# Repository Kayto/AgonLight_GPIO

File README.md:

# AgonLight_GPIO

## Background
Agon Light is a compact low-cost board that is both a microcomputer and a BASIC-programmed microcontroller. It is intended to be easily hackable and allow interfacing with the outside world. It features 20x GPIO, plus SPI, I2C, UART for serial communication and allows a great opportunity for learning and experimentation.

## Introduction 

This repo is intended to provide some simple add on boards for gpio examples and experiments. Although I am of the 8 bit vintage, I consider myself a novice. I enjoy hardware making as a way to better understand the inner hardware workings and to ultimately improve my coding. All is a work in progress and is open to contributions and ideas, within the stated aims and limitations of this project.

## Aims
* Provide a range of simple IO hardware to aid coding in BBC BASIC.
* To be useful in gaining a general understanding of GPIO usage and real world interfacing.
* Stick to the general GPIOs only.
* Avoid cables and breadboards and try to fit a standardised form factor. In this case a plugable "faceplate" for the exiting gpio port. The board should avoid constraining any existing ports and access.
* Ideally, provide onboard visual feedback to aid learning.
* Avoid additional hardware processing on the add on board. Keeping access to the low level hardware prevents adding more complications when learning. I.e. GALs, additional controller ICs are to be avoided.

## The PCBs

KiCad, Schematics and Gerbers are provided. Renders of the boards are shown in the KiCad directory. Please review before making a commitment. No warranties or support are provided. As of this date PCBs are not yet tested but I will mark as such once done.

#### #1 - The Blinkenlight. - tested working

Every 8 bit computer needs blinky lights. Not only do they look like good, they are useful for debugging and understanding what is going on at a bit level.
The Blinkenlight PCB is pretty much the breadboard example from the official documentation but without the fiddly wires. It directly plugs into the GPIO header and provides an easily viewable "faceplate". This presents the form for future boards.

#### #2 - 7 segment display. - tested working

This is a single 7 segment display linked to the Port C GPIOs. Allows a simple message display with a delay. Ok its only single digits but something to build on.
A caution on this is that you need a 7 segment display to suit the pin out (they do vary). Review the schematics, Pin 3 and 8 are power.I have provided a solder jumper for setting of common anode and common cathode displays. Note that for common anode the coding assumes a LOW signal for on and HIGH for off.

#### #3 - Double Seven

**In progress.**

This is a **double** 7 segment display linked to the Port C GPIOs for data and 2No. Port D GPIOs to do the multiplexing.
To save space resistor networks are used instead of individual resistors.

#### #4 - Moody. - tested working

This is an RGB LED linked to the Port C GPIOs, 2No. push buttons are also provided. The two push buttons on PC_3 and PC_4 are to establish some input and mode switching capability. 

## The Code

I have created some code to introduce the boards. As said, coding is not my strength so excuse the code, in some cases its not a great example but enough to get things going and for a challenge to improve.
To view the code add the .BBC files to the SD card and load via BBC BASIC then type LIST.

| Board | Code | Description |
|:----------|:-------------|:-----|
|[#1_Blinkenlight](https://github.com/Kayto/AgonLight_GPIO/tree/main/KiCad/%231_Blinkenlight) | [PortC_blink.bbc](https://github.com/Kayto/AgonLight_GPIO/tree/main/Code) | select individual LEDs, set number of blinks and speed. |
|[#1_Blinkenlight](https://github.com/Kayto/AgonLight_GPIO/tree/main/KiCad/%231_Blinkenlight) | [gpioknight.bbc](https://github.com/Kayto/AgonLight_GPIO/tree/main/Code)| Some blinky patterns. Excuse the code, its a bad example with lots of inefficient duplication to get things done. The **challenge** is open to simplify this, perhaps a data array for the gpio commands and a single procedure for the delay?|
|[#1_Blinkenlight](https://github.com/Kayto/AgonLight_GPIO/tree/main/KiCad/%231_Blinkenlight) | [random8blink.bbc](https://github.com/Kayto/AgonLight_GPIO/tree/main/Code)| An easy change to PortC-Blink, uses the random function and fixed blink speed to just randomly blink the 8 LEDs!|
|[#2_seven_segment](https://github.com/Kayto/AgonLight_GPIO/tree/main/KiCad/%232_7Segment)|  [diceroll.bbc](https://github.com/Kayto/AgonLight_GPIO/tree/main/Code) | A random 1-6 generator for board games, handy. | 
|[#2_seven_segment](https://github.com/Kayto/AgonLight_GPIO/tree/main/KiCad/%232_7Segment)|  [counter.bbc](https://github.com/Kayto/AgonLight_GPIO/tree/main/Code) | A single digit counter, you're welcome. | 
|[#4_Moody](https://github.com/Kayto/AgonLight_GPIO/tree/main/KiCad/%234_Moody)|  [moodyfade.bbc](https://github.com/Kayto/AgonLight_GPIO/tree/main/Code) | An RGB fade using some crude PWM in BBC BASIC. | 
|[#4_Moody](https://github.com/Kayto/AgonLight_GPIO/tree/main/KiCad/%234_Moody)|  [moodybutton.bbc](https://github.com/Kayto/AgonLight_GPIO/tree/main/Code) | The RGB fade but now includes buttons. Button A for on and off. Button B to increase the fade speed.| 

## Disclaimer & Credits

Just a note that I am not in any way affiliated or linked with the Agon project.
I am just an aspiring maker, sharing hobbyist builds.
Thanks to the Agon project and supporters.

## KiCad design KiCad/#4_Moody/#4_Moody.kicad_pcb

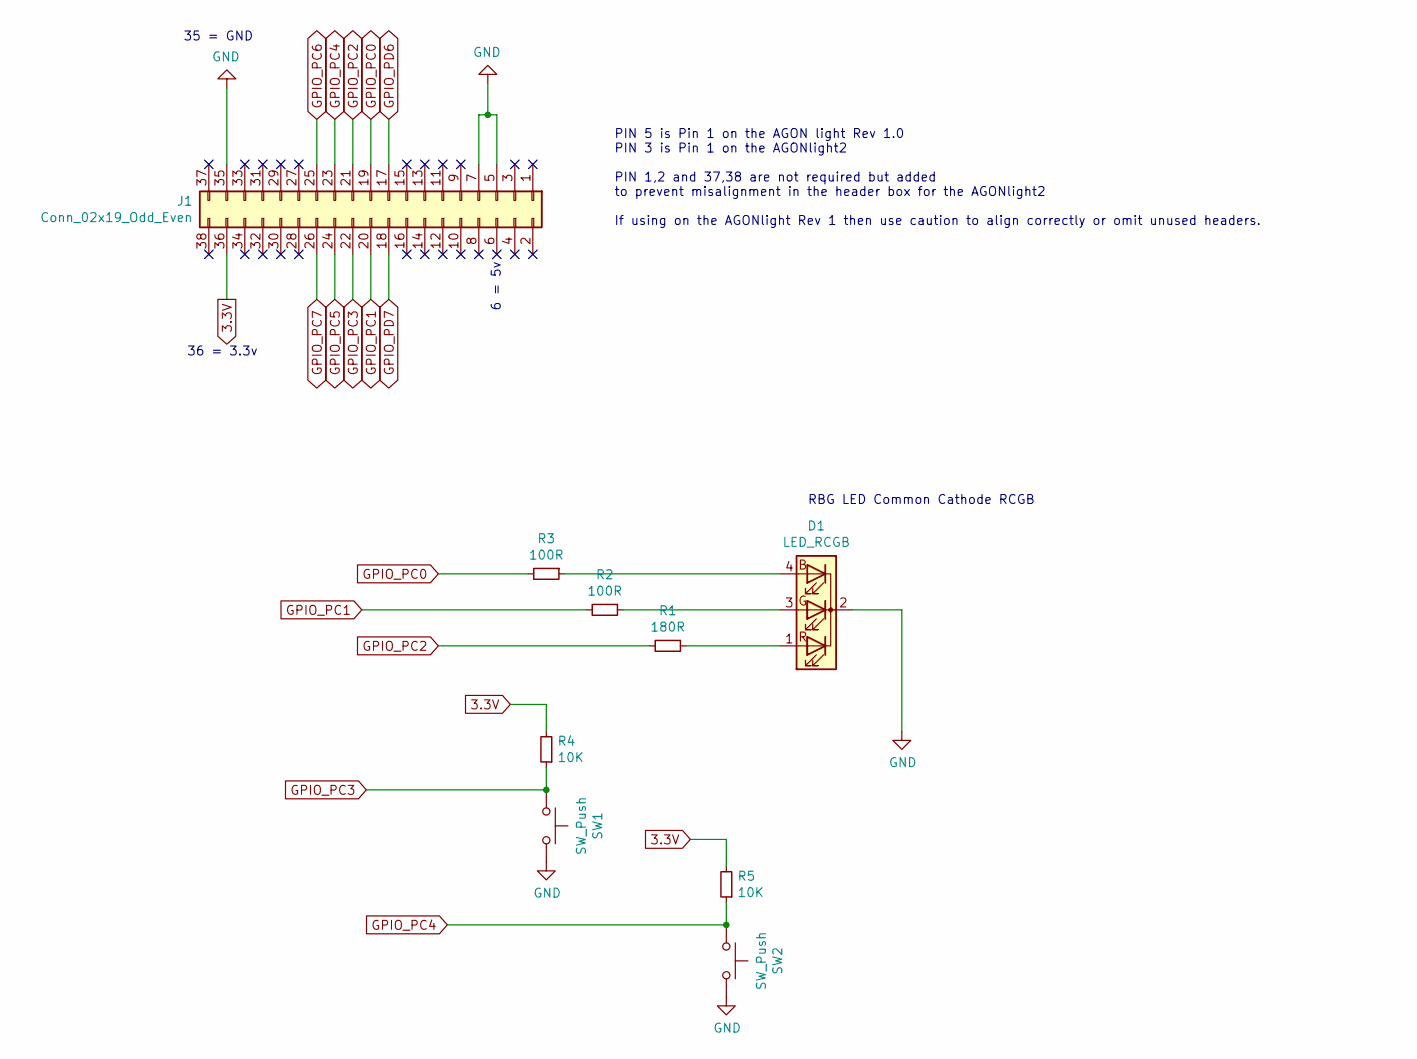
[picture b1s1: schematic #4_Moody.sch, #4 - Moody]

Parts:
D1: LED_RCGB; LED_D5.0mm-4_RGB
J1: Conn_02x19_Odd_Even; PinSocket_2x19_P2.54mm_Vertical
R1: 180R; R_Axial_DIN0207_L6.3mm_D2.5mm_P7.62mm_Horizontal
R2, R3: 100R; R_Axial_DIN0207_L6.3mm_D2.5mm_P7.62mm_Horizontal
R4, R5: 10K; R_Axial_DIN0207_L6.3mm_D2.5mm_P7.62mm_Horizontal
SW1, SW2: SW_Push; SW_PUSH_6mm_H4.3mm

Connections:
3.3V: J1.36, R4.2, R5.2
GND: D1.2 (K), J1.5, J1.7, J1.35, SW1.2, SW2.2
GPIO_PC0: J1.19, R3.2
GPIO_PC1: J1.20, R2.2
GPIO_PC2: J1.21, R1.2
GPIO_PC3: J1.22, R4.1, SW1.1
GPIO_PC4: J1.23, R5.1, SW2.1
GPIO_PC5: J1.24
GPIO_PC6: J1.25
GPIO_PC7: J1.26
GPIO_PD6: J1.17
GPIO_PD7: J1.18
unnamed: D1.1 (RA), R1.1
unnamed: D1.3 (GA), R2.1
unnamed: D1.4 (BA), R3.1

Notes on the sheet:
PIN 5 is Pin 1 on the AGON light Rev 1.0 PIN 3 is Pin 1 on the AGONlight2 PIN 1,2 and 37,38 are not required but added to prevent misalignment in the header box for the AGONlight2 If using on the AGONlight Rev 1 then use caution to align correctly or omit unused headers.
35 = GND
36 = 3.3v
6 = 5v
RBG LED Common Cathode RCGB

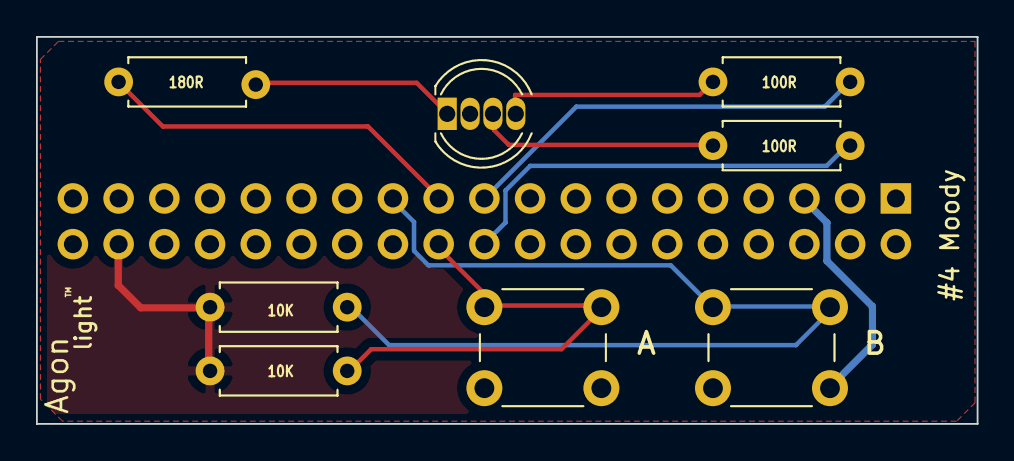
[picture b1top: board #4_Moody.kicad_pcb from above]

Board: 2 copper layers, 52.3 x 21.5 mm, 9 parts (1 on the bottom side), 10 nets.

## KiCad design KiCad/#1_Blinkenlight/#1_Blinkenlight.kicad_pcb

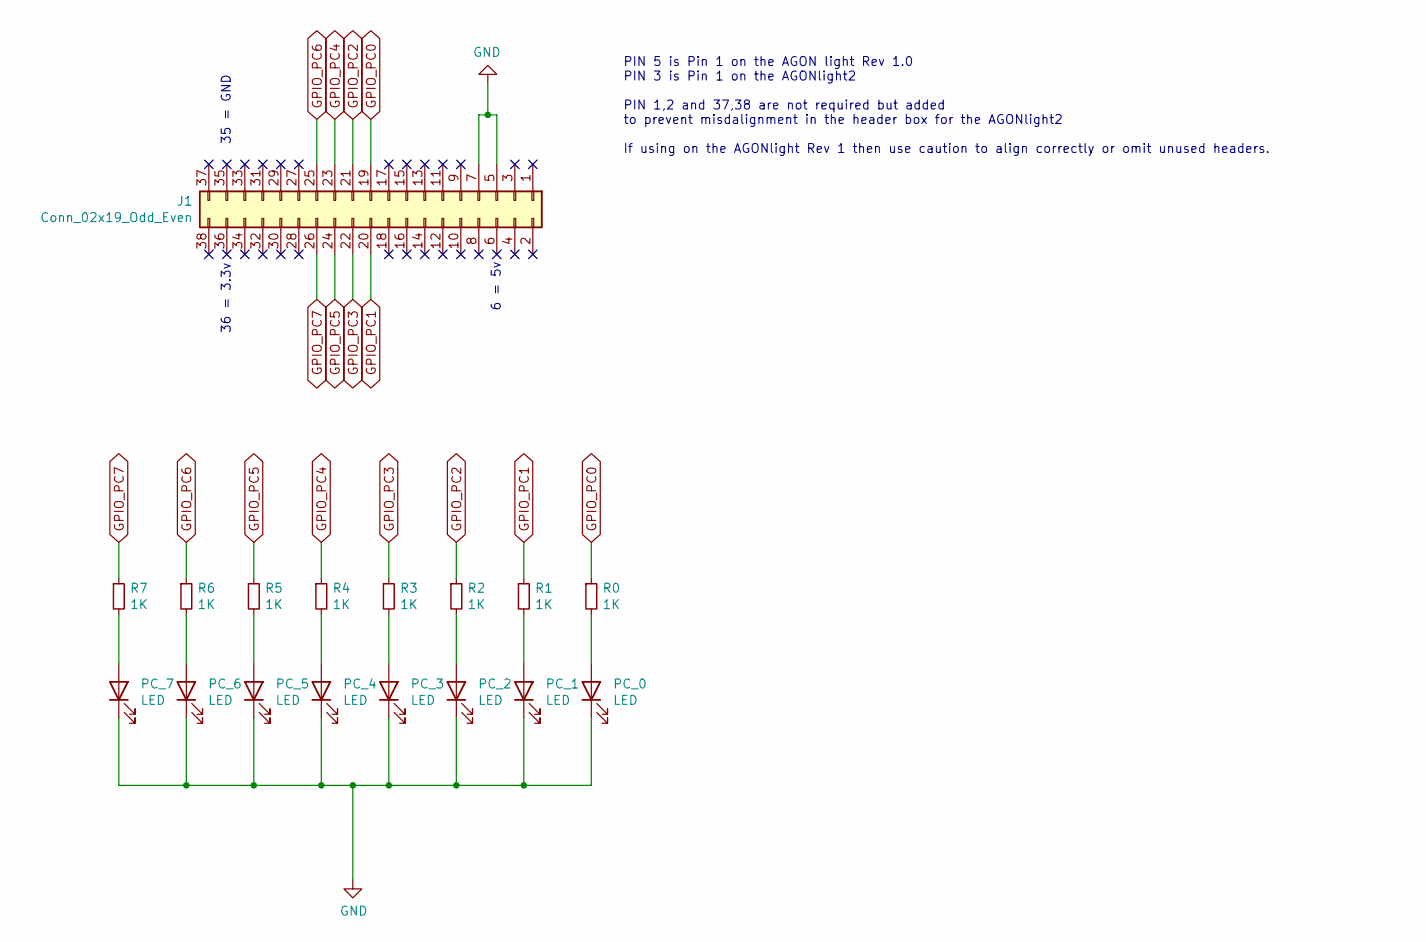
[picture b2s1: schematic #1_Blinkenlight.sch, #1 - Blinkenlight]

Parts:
J1: Conn_02x19_Odd_Even; PinSocket_2x19_P2.54mm_Vertical
PC_0, PC_1, PC_2, PC_3, PC_4, PC_5, PC_6, PC_7: LED; LED_D3.0mm
R0, R1, R2, R3, R4, R5, R6, R7: 1K; R_Axial_DIN0207_L6.3mm_D2.5mm_P7.62mm_Horizontal

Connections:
GND: J1.5, J1.7, PC_0.1 (K), PC_1.1 (K), PC_2.1 (K), PC_3.1 (K), PC_4.1 (K), PC_5.1 (K), PC_6.1 (K), PC_7.1 (K)
GPIO_PC0: J1.19, R0.1
GPIO_PC1: J1.20, R1.1
GPIO_PC2: J1.21, R2.1
GPIO_PC3: J1.22, R3.1
GPIO_PC4: J1.23, R4.1
GPIO_PC5: J1.24, R5.1
GPIO_PC6: J1.25, R6.1
GPIO_PC7: J1.26, R7.1
unnamed: PC_0.2 (A), R0.2
unnamed: PC_1.2 (A), R1.2
unnamed: PC_2.2 (A), R2.2
unnamed: PC_3.2 (A), R3.2
unnamed: PC_4.2 (A), R4.2
unnamed: PC_5.2 (A), R5.2
unnamed: PC_6.2 (A), R6.2
unnamed: PC_7.2 (A), R7.2

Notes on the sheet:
PIN 5 is Pin 1 on the AGON light Rev 1.0 PIN 3 is Pin 1 on the AGONlight2 PIN 1,2 and 37,38 are not required but added to prevent misdalignment in the header box for the AGONlight2 If using on the AGONlight Rev 1 then use caution to align correctly or omit unused headers.
35 = GND
36 = 3.3v
6 = 5v

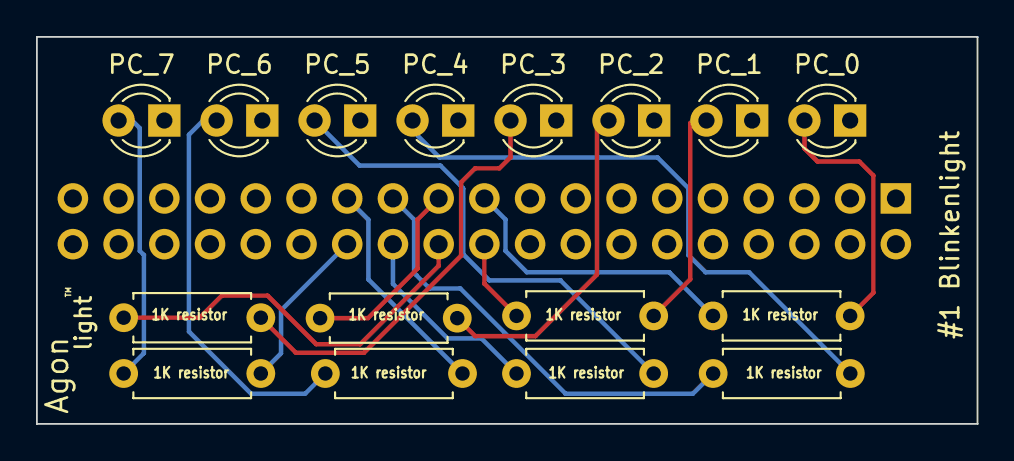
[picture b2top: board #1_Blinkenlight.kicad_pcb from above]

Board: 2 copper layers, 52.3 x 21.5 mm, 17 parts (1 on the bottom side), 17 nets.

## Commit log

2023-04-10 Code Added
2023-04-10 KiCad and Gerbers added
2023-04-10 Update LICENSE
2023-04-12 #2 7 segment PCB added
2023-04-12 Silk screen
2023-04-15 7segment code additions
2023-04-17 Images added
2023-04-30 #4 Moddy added WIP
2023-05-11 Gerbers
2023-05-18 Blinkenlight schematic correction
2023-05-21 Schematics moved.
2023-05-24 Code updates
